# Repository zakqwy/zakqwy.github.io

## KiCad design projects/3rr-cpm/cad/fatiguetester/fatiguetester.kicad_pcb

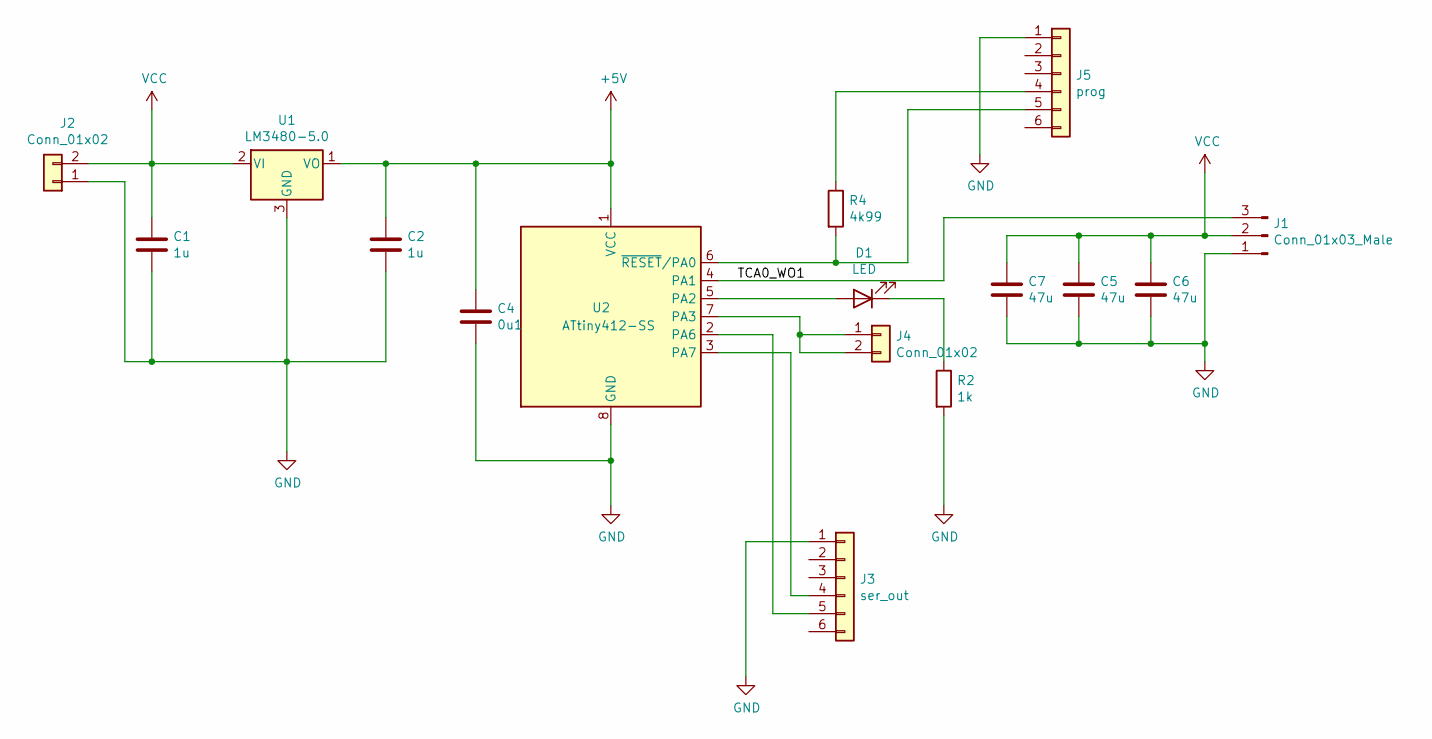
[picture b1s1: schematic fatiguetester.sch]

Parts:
C1, C2: 1u; fab_C_1206
C4: 0u1; fab_C_1206
C5, C6, C7: 47u; fab_R_1206
D1: LED; fab_LED_1206
J1: Conn_01x03_Male; CONN_SERVO_SMT
J2: Conn_01x02; BarrelJack_CLIFF_FC681465S_SMT_Horizontal
J3: ser_out; fab_CONN_1x06_SMD
J4: Conn_01x02; CONN_DCJACK_2-4mm
J5: prog; fab_CONN_1x06_SMD
R2: 1k; fab_R_1206
R4: 4k99; fab_R_1206
U1: LM3480-5.0; fab_SMD_SOT23
U2: ATtiny412-SS; fab_IC_SOIC8

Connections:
+5V: C2.1, C4.1, U1.1 (VO), U2.1 (VCC)
/TCA0_WO1: J1.3, U2.4 (PA1)
GND: C1.2, C2.2, C4.2, C5.2, C6.2, C7.2, J1.1, J2.1, J3.1, J5.1, R2.2, U1.3 (GND), U2.8 (GND)
unnamed: D1.1 (K), R2.1
unnamed: D1.2 (A), U2.5 (PA2)
unnamed: J3.4, U2.3 (PA7)
unnamed: J3.5, U2.2 (PA6)
unnamed: J4.1, J4.2, U2.7 (PA3)
unnamed: J5.4, R4.1
unnamed: J5.5, R4.2, U2.6 (~RESET~/PA0)
VCC: C1.1, C5.1, C6.1, C7.1, J1.2, J2.2, U1.2 (VI)

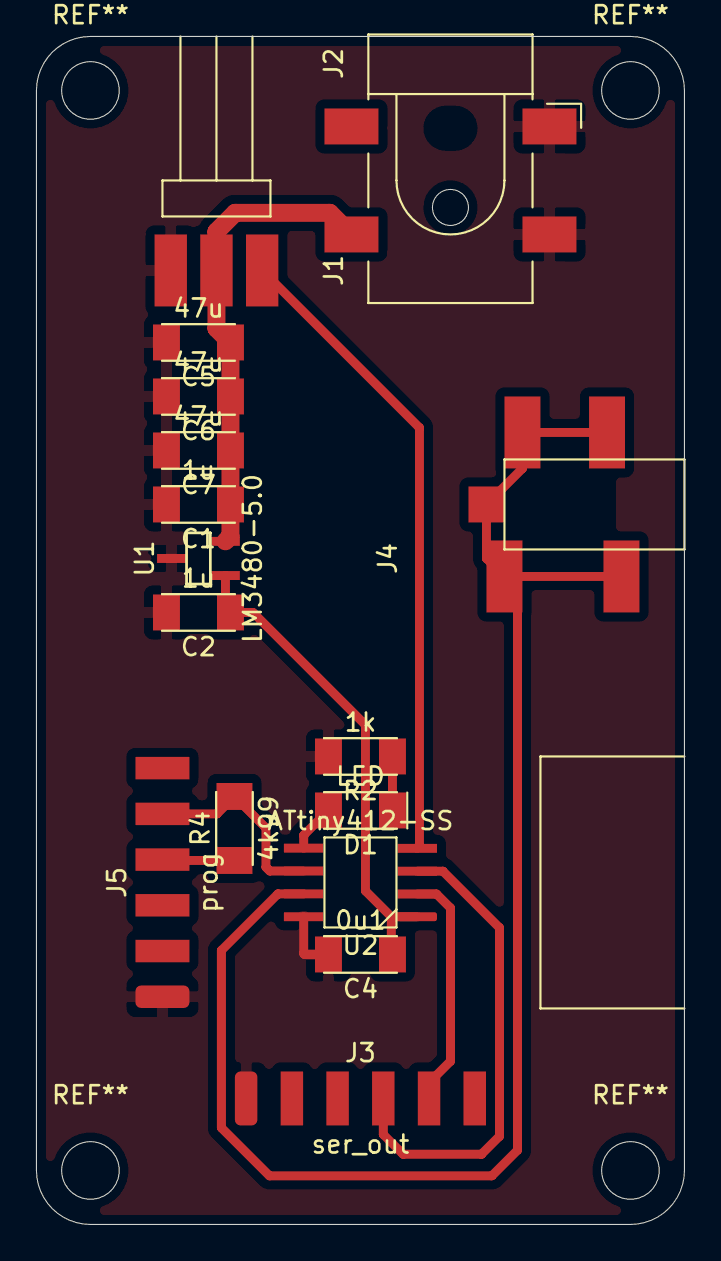
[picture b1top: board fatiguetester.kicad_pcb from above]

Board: 2 copper layers, 36.0 x 66.0 mm, 16 parts (0 on the bottom side), 11 nets.

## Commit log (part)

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2018-09-17 added README.md and LICENSE
2018-09-17 Create CNAME
2018-09-17 Update CNAME
2018-09-17 CNAME change
2018-09-17 removed CNAME
2018-09-17 readme update
2018-09-17 jekyll?
2018-09-17 Set theme jekyll-theme-cayman
2018-09-17 remove local copy
2018-09-17 updated _config.yml
2018-09-17 added jekyll front matter
2018-09-18 removed unnecessary html from index
2018-09-18 tried cayman theme title/description
2018-09-18 changed to Markdown for index. added Gemfile, etc
2018-09-18 added .gitignore
2018-10-07 added detail pages and more images. continued work on descriptions.
2018-11-16 updates to electronics section
2018-11-16 broke out novelty soldering. more pictures, more descriptions, etc
2018-11-21 added a bit of content
2018-11-21 more new content, added resume
2018-11-24 more info on neurobytes section
2018-11-26 updated resume and neurobytes section. more pics.
2018-11-27 Update neurobytes.md
    spelling ugh
2019-09-14 updated about.md
2022-01-06 test site
2022-01-06 move to new design, content, updates, etc
2022-01-07 mobile fix
2022-01-07 mobile fix 2
2022-01-07 mobile fix 3
2022-01-07 add responsiveness to project pages
2022-08-15 2022 woodland creatures
2023-03-24 add TPZ page, mirror other pages, add lego flexures, etc.
2023-03-24 added mom-timer
2023-03-24 added supercon badge card reader
2023-03-30 clock-one documentation
2023-03-30 update thumbnail for TPZ
2023-04-17 tpz MiR updates
2023-05-13 laser lathe
2023-05-15 laser lathe updates, bikelight addition
2023-05-21 diamond laser lathe documentation updates
2023-05-30 laser lathe documentation
2023-06-03 2023 birds
2023-06-03 resume, location update
2023-06-03 favicons ugh why didn't I use a CMS
2023-06-03 update tpz thumbnail
2023-06-05 bird
2023-07-06 loudinator details
2023-07-14 update persistence-of-vision
2023-07-14 persistence-of-vision updates
2023-07-14 documentation updates
2023-07-14 persistence-of-vision documentation updates
2023-07-14 proofreading
2023-07-16 beat flower documentation
2023-07-17 beat flower updates
2023-08-17 add cv, updates
2023-09-24 fresh birds
2023-09-30 link to caning peg lattices repo
2024-01-01 more titles
2024-03-10 haystack winter meal annunciator thumbnail
2024-03-10 thumbnail for tpz-usb
2024-05-29 Bird Alert
2024-06-01 hummingbird
2024-06-07 birds, bugs
2024-06-13 clip-os!
2024-07-08 fresh bird
2024-07-08 fresher bird
2024-07-08 yes birds
2024-09-01 woodland creatures late summer '24
2024-09-27 add flip pin laser lattices, reorg other 2024 things
2024-11-03 add circuit graver
2024-11-03 update date
2025-05-05 plattice
2025-05-06 plattice docs
2025-05-06 update date, jerb
2025-05-06 poking at css
2025-06-22 a bunch of critters
2025-06-22 2025 friends
2025-06-26 sludge craft
2025-06-26 formatting
2025-06-26 slude craft draft
2025-06-26 Rename raw-sludge.JPG to raw-sludge.jpg
    fix name
2025-06-26 Rename sem-setup.JPG to sem-setup.jpg
    fix name
2025-06-26 add vids
2025-06-26 buh JPG-->jpg :-/
2025-06-26 vids, minor edits
2025-06-26 links
2025-06-27 sludge craft updates
2025-06-27 sludge craft link git push
2025-06-27 minor edits
2025-06-27 omg name update sludge-brain
2025-06-28 woodland creaturessssss
2025-07-04 woodland creatures, formatting
2026-05-25 new zach photo
